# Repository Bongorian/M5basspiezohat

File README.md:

# M5basspiezohat

M5StickS3のHat2に接続する、ベース用の5チャンネル・ピエゾ入力基板。弦ごとの独立したピエゾ信号を高入力抵抗のバッファと音声ADCで処理し、TDMで本体へ送る。

本体で音程検出とUSB MIDI出力を行うESP-IDFファームウェアを含む。基板とファームウェアは実機未検証のR1試作版。

```text
独立ピエゾ ×4〜5 → 保護・バッファ・LPF → ES7210 ×2
                                      → TDM → M5StickS3
                                               → 音程検出・USB MIDI
```

## 仕様

| 項目 | R1 |
| --- | --- |
| 接続先 | M5StickS3 Hat2 |
| 入力 | 独立ピエゾ最大5チャンネル、内部SIG/GNDはんだパッド |
| ADC | ES7210×2、TDMカスケード接続 |
| 電源 | Hat2 EXT_5V、基板内でアナログ／デジタル3.3Vを生成 |
| 基板 | 21×38×1.0mm、4層、四隅R1mm |
| 実装 | 表面PCBA 101点。裏面は裸銅箔テストパッド4点 |
| 手実装 | ヘッダJ6、ピエゾ配線 |
| 筐体の設計範囲 | Hat単体・コネクタ込み48×24×15mm以内 |

## 設計データの利用

1. [基板仕様・接続表](hardware/sticks3-piezo-hat/README.md)で電源、Hat2端子、ピエゾ入力を確認する。
2. KiCad 9で [プロジェクト](hardware/sticks3-piezo-hat/sticks3-piezo-hat.kicad_pro)を開く。[回路図](hardware/sticks3-piezo-hat/sticks3-piezo-hat.kicad_sch)と[配線済み基板](hardware/sticks3-piezo-hat/sticks3-piezo-hat.kicad_pcb)が編集元。
3. 製造には [JLCPCB用データ一式](hardware/sticks3-piezo-hat/release/PCBA_JLCPCB.zip)と[製造・組立手順](hardware/sticks3-piezo-hat/manufacturing.md)を使用する。BOM、CPL、手実装部品の一覧を含む。
4. 変更後は[再生成・検査手順](hardware/sticks3-piezo-hat/README.md#ソースと再生成)に従い、製造データを再出力する。
5. [ファームウェアの導入・操作手順](firmware/README.md)に従ってM5StickS3へ書き込み、入力スロットを確認する。標準は5弦・共通MIDIチャンネル1・起動時ミュート・高速開始設定。[標準設定の書き込み用ZIP](firmware/release/m5basspiezohat-sticks3-0.2.1.zip)も使用できる。

## 検証状況

KiCad 9.0.9で未接続0件、DRC違反0件、ERC違反0件。回路図・基板・設計マニフェストの318接続を照合済み。[検査記録](hardware/sticks3-piezo-hat/validation.md)を参照。

Hat2ヘッダの嵌合、TDM取得、Low Bまでの周波数応答、弦間の振動漏れ、音程検出の遅延は未検証。[ファームウェア設計・評価手順](docs/firmware-design.md)に取得条件と評価項目を記載している。標準のUSBデバイスモードはUSBホストへ接続する。ホストモードも実装しているが、StickS3はUSB-Cへ給電しないため、音源側への外部VBUS給電と適切な接続回路が必要。

ファームウェアはESP-IDF v5.4.2でESP32-S3向けビルドを確認。合成信号による音程・発音・MIDIルーティングのホストテストを通過している。[CI](https://github.com/Bongorian/M5basspiezohat/actions/workflows/firmware.yml)でもビルドとテストを実行する。

[クロストーク分離・校正学習の検討](docs/crosstalk-separation.md)には固定行列とFIR分離の導入条件を記載。同期CSVから固定混合行列を学習するオフライン評価ツールを含む。リアルタイム分離と実機学習は未実装。

[Grove接続の外付けUSB MIDIホスト案](docs/grove-usb-midi-host.md)に、別USB端子を追加して本体USB-Cを維持する構成、通信・給電条件、LCSC部品候補を記載している。外部基板は未製作。

[筐体モデル](mechanical/sticks3-hat-concept.md)は寸法・保持構造の検討用。蓋と下端受けの固定方法、ケーブル出口は未設計。

## ファイル構成

| ディレクトリ | 内容 |
| --- | --- |
| `hardware/sticks3-piezo-hat/` | KiCad編集元、プロジェクト内ライブラリ、BOM、生成・検査ツール |
| `hardware/sticks3-piezo-hat/release/` | Gerber、PCBA用BOM/CPL、組立位置図、製造用ZIP |
| `mechanical/` | Blender筐体検討モデル、寸法計算、生成スクリプト |
| `docs/` | ファームウェア設計と評価手順 |
| `firmware/` | ESP-IDFアプリ、音程検出、USB MIDI、診断ツール、ホストテスト、書き込み用ZIP |

## ライセンス

KiCad由来のライブラリ・モデルとファームウェア依存ライブラリの出典・ライセンスは [NOTICE.md](NOTICE.md) を参照。プロジェクト独自部分の利用ライセンスは未指定。

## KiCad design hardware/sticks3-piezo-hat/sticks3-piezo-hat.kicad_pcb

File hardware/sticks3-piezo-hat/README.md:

# M5basspiezohat R1 — 基板仕様

弦ごとに独立したピエゾを最大5入力受け、ES7210×2のTDM出力をM5StickS3へ渡す。[付属ファームウェア](../../firmware/README.md)が音程検出とUSB MIDI出力を行う。基板・ファームウェアとも実機未検証。

**筐体の設計範囲：Hat単体・コネクタ込み48×24×15mm以内。** 基板は21×38×1.0mm、四隅R1mm、4層。ケース本体41.1×23.8×14.8mm。候補ヘッダC53207371のメーカー図面に基づくコネクタ込み公称長47.3mm、公差予算込み47.9mm。実機嵌合・造形精度は未確認で、寸法保証ではない。基板に固定穴・切り欠きはなく、筐体の左右ガイド溝と上下の受けで支える機構案。受けと蓋の留め方は未設計。[機構案](../../mechanical/sticks3-hat-concept.md)を参照。

## 設計検査

KiCad 9.0.9で未接続0件、DRC違反0件、回路図ERC違反0件。配線済み基板は [sticks3-piezo-hat.kicad_pcb](sticks3-piezo-hat.kicad_pcb)。2410配線セグメント／161ビア、回路図／基板／設計マニフェストの318接続が一致。部品本体は表面のみ、裏面はTP1〜4の裸銅箔。内層GND面の信号線は0、SMDパッドとビア穴の重なりは0。

[JLCPCB用データ一式](release/README.md)：[Gerber ZIP](release/Gerber_JLCPCB.zip)、[PCBA BOM](release/BOM_JLCPCB.csv)、[CPL](release/CPL_JLCPCB.csv)、[組立位置図](release/assembly-front.png)。BOMとCPLは101個の部品名が完全一致し、全点Top。CPLは品番別の回転補正を適用済み。D1〜D5もPCBA対象。J6とピエゾ線は手実装。U4の割り込み出力（13番ピン）はNC。ADC初期設定では割り込みを無効にする。

最小配線幅／間隔0.10／0.10mm、貫通ビア外径0.40mm・穴0.20mm、表裏テント、マスク開口1:1。[JLCPCBの能力表](https://jlcpcb.com/capabilities/pcb-capabilities)に対応するが、外径0.45mm未満・穴0.20mmのビアは追加料金対象なので、注文時に小径ビアの条件を指定する。製造条件と手実装の手順は [manufacturing.md](manufacturing.md)、検査記録は [validation.md](validation.md) を参照。

## 回路

| 回路 | 仕様 |
| --- | --- |
| 入力 | SIG/GND ×5組、内部はんだパッド、穴0.8mm・径1.8mm |
| 保護 | 47kΩ直列＋低漏れBAV199Wの2ダイオードクランプ |
| 入力負荷 | 10MΩを2個直列にした20MΩでVMIDへバイアス |
| バッファ | TLV9064IRTER ×2、3×3mm WQFN、利得1 |
| 中点 | 47kΩ分圧＋1µF→U2Bバッファ、約1.65V |
| LPF | 各入力1kΩ／47nFを2段、受動回路 |
| ADC結合 | P側10µF直列、N側10µFでAC接地。ADCのDCバイアスを分離 |
| ADC | ES7210 ×2、入力8スロット、うち5スロットを音程解析 |
| 電源 | EXT_5V→AP2112K-3.3 ×2、3V3A／3V3D |
| クロック | MCLK/BCLK/WSに33Ω、データ／カスケードにも33Ω |

受動LPFは2段の間にバッファがないため、独立したRCを2個掛けた特性と異なる。ADC入力負荷を無視した等しいR/Cの伝達は `1/(1+3sRC+(sRC)^2)`、合成-3dB周波数は約1.27kHz。R=1kΩ、C=47nFによる計算値で、ADC入力インピーダンスを含む実際の応答は測定する。アタックと倍音を残せるか、ADC内PGA・HPFと合わせて確認する。

Low B・30.87Hzを保つため、ピエゾ容量、20MΩ負荷、AC結合容量、ADC内部HPFをまとめて評価する。低漏れ保護の代わりに汎用BAV99や漏れの大きいSchottkyへ無確認で置き換えない。高抵抗入力付近は組み立て後にフラックスを清掃する。無給電時のピエゾ電圧による電源への回り込みも試験する。

## LCSC部品と実装分担

| 部品 | LCSC | 個数 | 分担 |
| --- | --- | ---: | --- |
| ES7210・4入力ADC | [C365743](https://www.lcsc.com/product-detail/C365743.html) | 2 | PCBA |
| TLV9064IRTER・3×3mm WQFN | [C882406](https://www.lcsc.com/product-detail/C882406.html) | 2 | PCBA |
| AP2112K-3.3TRG1 | [C51118](https://www.lcsc.com/product-detail/C51118.html) | 2 | PCBA |
| BAV199W・CBI・SOT-323 | [C51315120](https://www.lcsc.com/product-detail/C51315120.html) | 5 | PCBA |
| 10MΩ・SAE・0402 | [C54531017](https://www.lcsc.com/product-detail/C54531017.html) | 10 | PCBA |
| 1kΩ・0402 | [C11702](https://www.lcsc.com/product-detail/C11702.html) | 12 | PCBA |
| 33Ω・0402 | [C25105](https://www.lcsc.com/product-detail/C25105.html) | 5 | PCBA |
| 47kΩ・0603 | [C25819](https://www.lcsc.com/product-detail/C25819.html) | 8 | PCBA |
| 100nF・0402 | [C1525](https://www.lcsc.com/product-detail/C1525.html) | 6 | PCBA |
| 47nF・0402 | [C82219](https://www.lcsc.com/product-detail/C82219.html) | 10 | PCBA |
| 1µF・0402 | [C52923](https://www.lcsc.com/product-detail/C52923.html) | 25 | PCBA |
| 10µF・0603 | [C19702](https://www.lcsc.com/product-detail/C19702.html) | 14 | PCBA |
| 2×8・2.54mm L型ヘッダ・BXCONN | [C53207371](https://www.lcsc.com/product-detail/C53207371.html)・候補、実機嵌合未確認 | 1 | 手はんだ |
| ピエゾ線 | 基板内パッドへ接続 | 5組 | 手はんだ |

部品番号・数量・実装分担は [BOM_full.csv](BOM_full.csv) を基準とする。PCBAには [BOM_JLCPCB.csv](BOM_JLCPCB.csv)、手実装には [HAND_ASSEMBLY.csv](HAND_ASSEMBLY.csv) を使用する。LCSCの販売在庫とJLCPCBの実装用在庫・部品区分・調達価格は個別に確認する。

## Hat2接続

J6番号は **M5の外部Hat2端子表の番号**。M5内部回路図のCN2番号とは異なる。

| J6 | M5信号 | 本基板 |
| ---: | --- | --- |
| 1 | GND | GND |
| 2 | G5 | SCL |
| 3 | EXT_5V | 5V_HAT |
| 4 | G4 | SDA |
| 6 | G6 | WS |
| 7 | G1 | MCLK |
| 8 | G7 | BCLK |
| 9 | G8 | TDM DATA |
| その他 | BOOT/BAT/3V3/5VIN等 | 未接続 |

この番号とGPIOは [M5公式端子表](https://docs.m5stack.com/en/core/StickS3) に基づく。標準ヘッダのピン1マークと本体のGND位置は、選定した部品の視方向と実物で照合する。嵌合と挿入長は実機で確認する。

`M5.begin()`後、`M5.Power.setExtOutput(true)`でEXT_5Vを出力にする。本体GPIOは3.3V。EXT_5Vを出力にした状態で、その端子へ別電源を接続しない。

ADCの7bit I²CアドレスはU3＝0x40、U4＝0x41を想定したAD0/AD1接続。アドレスは実機で確認する。U3 TDMOUT→33Ω→U4 TDMIN、U4 TDMOUT→33Ω→J6 DATA。共通MCLK/BCLK/WSを使う。レジスタ設定は実機試験で確定する。

## 取得・MIDIの初期条件

16kS/s、8スロット×16bit、MCLK4.096MHz、BCLK2.048MHzを評価開始点とする。DMAは32フレーム×8本、合計4096B／16ms容量。2msごとに取得し、解析側へ渡す。詳細は [ファームウェア設計](../../docs/firmware-design.md) を参照。

Low Bの周期は約32.4ms。DMA待ちを短くしても、音程確定に必要な観測時間は残る。音声取得、音程解析、USB送信、音源発音の遅延を分けて測定する。USB MIDIは本体USB-Cを使い、音源のUSBホスト機能またはPC／USB MIDIホストを経由する。DIN出力回路はこのHatには載せていない。

## ソースと再生成

- `sticks3-piezo-hat.kicad_sch`：全ピンを明示した回路図
- `sticks3-piezo-hat.kicad_pcb`：配線済み最終基板
- `sticks3-piezo-hat-placement.kicad_pcb`：再生成用の配置版
- `PiezoHat.pretty/`、`PiezoHat.kicad_sym`：プロジェクト内ライブラリ
- `design.json`：ピン、型番、部品座標
- `BOM_JLCPCB.csv`：PCBA部品のみ、標準4列
- `jlc-rotation-corrections.json`：品番別のCPL回転補正。新しい品番へ変更したらプレビューを再確認
- `BOM_full.csv`、`HAND_ASSEMBLY.csv`：全調達／手実装
- `verify.py`、`verification.json`：接続と実装面の確認
- `preview/routed-front.png`、`preview/routed-board.glb`：最終基板の配線図・3D
- `release/`：Gerber、BOM、CPL、組立位置図、検査記録
- [ケースモデル](../../mechanical/sticks3-hat-concept.md)

KiCad 9.0.9の`kicad-cli`と`pcbnew`を読み込めるPythonが必要。Ubuntuでは`/usr/bin/python3`を使う。生成にはNumPy、図の出力にはPillow、補助ルータにはSciPyとC++17コンパイラを用意する。自動配線には別途`freerouting-cli`が必要。

```sh
cd hardware/sticks3-piezo-hat
/usr/bin/python3 generate.py
kicad-cli sch export netlist --format kicadxml -o schematic.xml sticks3-piezo-hat.kicad_sch
/usr/bin/python3 verify.py sticks3-piezo-hat-placement.kicad_pcb
/usr/bin/python3 route_compact.py sticks3-piezo-hat-placement.kicad_pcb NEW-routed.kicad_pcb
```

再生成は配置・回路図・BOMを上書きし、配線済み基板は別ファイルに保存する。KiCadのDSN出力へは0.127mm標準配線／0.10mm間隔、ビア径0.40mm・穴0.20mmを明示的に反映する。内層1はGND面、内層2は信号。QFN露出パッドの未充填ビアを禁止する。

## 組立・評価

[製造・組立手順](manufacturing.md)に従い、手実装部品とヘッダ方向を確認する。評価では電源・中点電圧、I²Cアドレス、ADC1個のTDM取得、2個のカスケード取得の順に確認する。ピエゾ接続後、Low Bの周波数応答、強いアタックでのクリップ、弦間漏れを測定する。

## 参照資料

メーカー資料：[ES7210レジスタ資料](https://files.waveshare.com/wiki/common/ES7210_DS.pdf)、[TLV9064](https://www.ti.com/lit/ds/symlink/tlv9064.pdf)、[CBI BAV199W](https://datasheet.lcsc.com/datasheet/pdf/08d81ae9ee2012e6b42c6110d851602f.pdf?productCode=C51315120)、[Espressif I²S/TDM/DMA](https://docs.espressif.com/projects/esp-idf/en/stable/esp32s3/api-reference/peripherals/i2s.html)。

## 製造データの再出力

リポジトリルートから実行する。配線済み基板を入力に、DRC／ERC・接続照合後、Gerber・BOM・CPL・ZIP・チェックサムを再出力する：

```sh
cd hardware/sticks3-piezo-hat
/usr/bin/python3 release.py
```

## 補助ルータ

`finish_route.py`用の補助ルータは `hardware/sticks3-piezo-hat/` で次のように構築する。生成・配線ツールは検討用で、毎回DRC／ERCと接続照合を行う。

```sh
mkdir -p .build
g++ -O3 -std=c++17 finish_astar.cpp -o .build/piezo-finish-astar
```

プロジェクト内のKiCad由来ライブラリについては [ライセンス文書](KICAD_LIBRARIES_LICENSE.md) と [出典](../../NOTICE.md) を参照。

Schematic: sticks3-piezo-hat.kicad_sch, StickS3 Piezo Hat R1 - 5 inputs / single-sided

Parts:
C1, C2, C32, C33, C43, C44: 100n; C_0402_1005Metric_AssemblyFront; LCSC C1525
C3, C4, C7, C8, C11, C12, C15, C16, C19, C20: 47n; C_0402_1005Metric_AssemblyFront; LCSC C82219
C5, C6, C9, C10, C13, C14, C17, C18, C21, C22, C51, C52, C53, C54: 10u; C_0603_1608Metric_AssemblyFront; LCSC C19702
C23, C24, C25, C26, C27, C28, C29, C30, C31, C34, C35, C36, C37, C38, C39, C40, C41, C42, C45, C46, C47, C48, C49, C50, C55: 1u; C_0402_1005Metric_AssemblyFront; LCSC C52923
D1, D2, D3, D4, D5: BAV199W; SOT-323_SC-70_AssemblyFront; LCSC C51315120
J1: PIEZO1; PiezoPair_P3.8
J2: PIEZO2; PiezoPair_P3.8
J3: PIEZO3; PiezoPair_P3.8
J4: PIEZO4; PiezoPair_P3.8
J5: PIEZO5; PiezoPair_P3.8
J6: HAT2_MANUAL; PinHeader_2x08_P2.54mm_Horizontal_AssemblyFront; LCSC C53207371
R1, R4, R7, R10, R13, R26, R28, R29: 47k; R_0603_1608Metric_AssemblyFront; LCSC C25819
R2, R3, R5, R6, R8, R9, R11, R12, R14, R15: 10M; R_0402_1005Metric_AssemblyFront; LCSC C54531017
R16, R17, R18, R19, R20, R21, R22, R23, R24, R25, R30, R31: 1k; R_0402_1005Metric_AssemblyFront; LCSC C11702
R32, R33, R34, R35, R36: 33R; R_0402_1005Metric_AssemblyFront; LCSC C25105
TP1: GND; TestPoint_Pad_D1.0mm_AssemblyFront
TP2: 3V3A; TestPoint_Pad_D1.0mm_AssemblyFront
TP3: 3V3D; TestPoint_Pad_D1.0mm_AssemblyFront
TP4: VMID; TestPoint_Pad_D1.0mm_AssemblyFront
U1, U2: TLV9064IRTER; QFN-16-1EP_3x3mm_P0.5mm_EP1.675x1.675mm_AssemblyFront; LCSC C882406
U3, U4: ES7210; ES7210_QFN32_4x4_P0.4_EP2.7; LCSC C365743
U5, U6: AP2112K-3.3TRG1; SOT-23-5_AssemblyFront; LCSC C51118

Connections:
3V3A: C1.1, C2.1, C30.1, C31.1, C41.1, C42.1, C52.1, D1.2 (K2/V+), D2.2 (K2/V+), D3.2 (K2/V+), D4.2 (K2/V+), D5.2 (K2/V+), R28.1, TP2.1, U1.2 (V+), U2.2 (V+), U3.22 (VDDA), U3.23 (VDDM), U4.22 (VDDA), U4.23 (VDDM), U5.5 (VOUT)
3V3D: C32.1, C33.1, C43.1, C44.1, C54.1, R26.2, R30.2, R31.2, TP3.1, U3.6 (VDDP), U3.7 (VDDD), U4.1 (AD0), U4.6 (VDDP), U4.7 (VDDD), U6.5 (VOUT)
5V_HAT: C51.1, C53.1, J6.3 (EXT_5V), U5.1 (VIN), U5.3 (EN), U6.1 (VIN), U6.3 (EN)
AIN1N: C6.1, U3.15 (MIC1N)
AIN1P: C5.2, U3.16 (MIC1P)
AIN2N: C10.1, U3.20 (MIC2N)
AIN2P: C9.2, U3.19 (MIC2P)
AIN3N: C14.1, U3.32 (MIC3N)
AIN3P: C13.2, U3.31 (MIC3P)
AIN4N: C18.1, U3.27 (MIC4N)
AIN4P: C17.2, U3.28 (MIC4P)
AIN5N: C22.1, U4.15 (MIC1N)
AIN5P: C21.2, U4.16 (MIC1P)
AIN6N: C46.1, U4.20 (MIC2N)
AIN6P: C45.1, U4.19 (MIC2P)
AIN7N: C48.1, U4.32 (MIC3N)
AIN7P: C47.1, U4.31 (MIC3P)
AIN8N: C50.1, U4.27 (MIC4N)
AIN8P: C49.1, U4.28 (MIC4P)
BCLK: R33.2, U3.9 (SCLK), U4.9 (SCLK)
BCLK_HAT: J6.8 (G7/BCLK), R33.1
BIAS1: R2.2, R3.1
BIAS2: R5.2, R6.1
BIAS3: R8.2, R9.1
BIAS4: R11.2, R12.1
BIAS5: R14.2, R15.1
BUF1: R16.1, U1.15 (OUTA), U1.16 (INA-)
BUF2: R18.1, U1.4 (INB-), U1.5 (OUTB)
BUF3: R20.1, U1.8 (OUTC), U1.9 (INC-)
BUF4: R22.1, U1.13 (IND-), U1.14 (OUTD)
BUF5: R24.1, U2.15 (OUTA), U2.16 (INA-)
CASCADE: R36.1, U3.11 (TDMOUT)
CASCADE_IN: R36.2, U4.12 (TDMIN)
GND: C1.2, C2.2, C3.2, C4.2, C6.2, C7.2, C8.2, C10.2, C11.2, C12.2, C14.2, C15.2, C16.2, C18.2, C19.2, C20.2, C22.2, C23.2, C24.2, C25.2, C26.2, C27.2, C28.2, C29.2, C30.2, C31.2, C32.2, C33.2, C34.2, C35.2, C36.2, C37.2, C38.2, C39.2, C40.2, C41.2, C42.2, C43.2, C44.2, C45.2, C46.2, C47.2, C48.2, C49.2, C50.2, C51.2, C52.2, C53.2, C54.2, C55.2, D1.1 (A1/GND), D2.1 (A1/GND), D3.1 (A1/GND), D4.1 (A1/GND), D5.1 (A1/GND), J1.2 (GND), J2.2 (GND), J3.2 (GND), J4.2 (GND), J5.2 (GND), J6.1 (GND), R29.2, TP1.1, U1.11 (V-), U1.17 (EP/V-), U2.11 (V-), U2.17 (EP/V-), U3.1 (AD0), U3.2 (AD1), U3.8 (GNDD), U3.12 (TDMIN), U3.21 (GNDA), U3.33 (EP), U4.2 (AD1), U4.8 (GNDD), U4.21 (GNDA), U4.33 (EP), U5.2 (GND), U6.2 (GND)
HI1: D1.3 (K1/A2/IN), R1.2, R2.1, U1.1 (INA+)
HI2: D2.3 (K1/A2/IN), R4.2, R5.1, U1.3 (INB+)
HI3: D3.3 (K1/A2/IN), R7.2, R8.1, U1.10 (INC+)
HI4: D4.3 (K1/A2/IN), R10.2, R11.1, U1.12 (IND+)
HI5: D5.3 (K1/A2/IN), R13.2, R14.1, U2.1 (INA+)
INT3: R26.1, U3.13 (INT)
LP1A: C3.1, R16.2, R17.1
LP1B: C4.1, C5.1, R17.2
LP2A: C7.1, R18.2, R19.1
LP2B: C8.1, C9.1, R19.2
LP3A: C11.1, R20.2, R21.1
LP3B: C12.1, C13.1, R21.2
LP4A: C15.1, R22.2, R23.1
LP4B: C16.1, C17.1, R23.2
LP5A: C19.1, R24.2, R25.1
LP5B: C20.1, C21.1, R25.2
MCLK: R32.2, U3.5 (MCLK), U4.5 (MCLK)
MCLK_HAT: J6.7 (G1/MCLK), R32.1
PZ1: J1.1 (SIG), R1.1
PZ2: J2.1 (SIG), R4.1
PZ3: J3.1 (SIG), R7.1
PZ4: J4.1 (SIG), R10.1
PZ5: J5.1 (SIG), R13.1
SCL: J6.2 (G5/SCL), R31.1, U3.4 (CCLK), U4.4 (CCLK)
SDA: J6.4 (G4/SDA), R30.1, U3.3 (CDATA), U4.3 (CDATA)
SPARE_C: U2.8 (OUTC), U2.9 (INC-)
SPARE_D: U2.13 (IND-), U2.14 (OUTD)
TDM_HAT: J6.9 (G8/DATA), R35.2
TDM_OUT: R35.1, U4.11 (TDMOUT)
U3_MICBIAS12: C25.1, U3.24 (MICBIAS12)
U3_MICBIAS34: C27.1, U3.26 (MICBIAS34)
U3_REFP12: C23.1, U3.17 (REFP12)
U3_REFP34: C28.1, U3.29 (REFP34)
U3_REFQ12: C24.1, U3.18 (REFQ12)
U3_REFQ34: C29.1, U3.30 (REFQ34)
U3_REFQM: C26.1, U3.25 (REFQM)
U4_MICBIAS12: C36.1, U4.24 (MICBIAS12)
U4_MICBIAS34: C38.1, U4.26 (MICBIAS34)
U4_REFP12: C34.1, U4.17 (REFP12)
U4_REFP34: C39.1, U4.29 (REFP34)
U4_REFQ12: C35.1, U4.18 (REFQ12)
U4_REFQ34: C40.1, U4.30 (REFQ34)
U4_REFQM: C37.1, U4.25 (REFQM)
VDIV: C55.1, R28.2, R29.1, U2.3 (INB+), U2.10 (INC+), U2.12 (IND+)
VMID: R3.2, R6.2, R9.2, R12.2, R15.2, TP4.1, U2.4 (INB-), U2.5 (OUTB)
WS: R34.2, U3.10 (LRCK), U4.10 (LRCK)
WS_HAT: J6.6 (G6/WS), R34.1

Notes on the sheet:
STRING 1: 20M load / unity buffer / passive two-pole LPF / AC isolated ADC
STRING 2: 20M load / unity buffer / passive two-pole LPF / AC isolated ADC
STRING 3: 20M load / unity buffer / passive two-pole LPF / AC isolated ADC
STRING 4: 20M load / unity buffer / passive two-pole LPF / AC isolated ADC
STRING 5: 20M load / unity buffer / passive two-pole LPF / AC isolated ADC
BUFFERS: U1 A-D = strings 1-4; U2 A = string 5; U2 B = VMID; C/D terminated
DECOUPLING / BIAS / CLOCK TERMINATION / TEST: all pins and nets explicit
ADC3 = address 0x40 / inputs 1-4; ADC4 = 0x41 / input 5 plus unused inputs 6-8

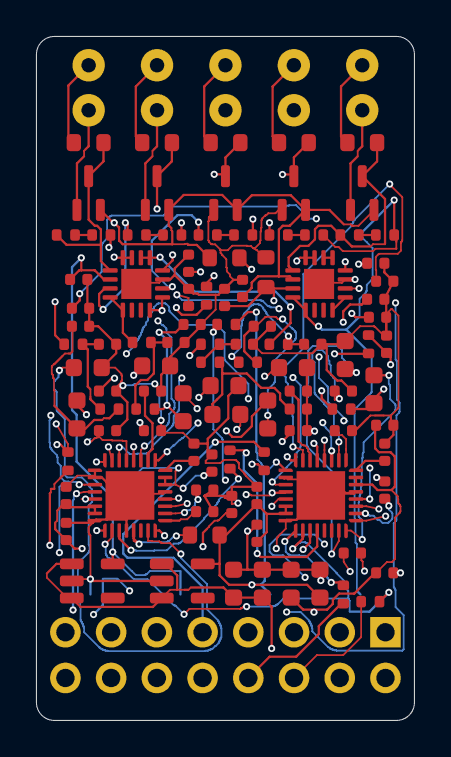
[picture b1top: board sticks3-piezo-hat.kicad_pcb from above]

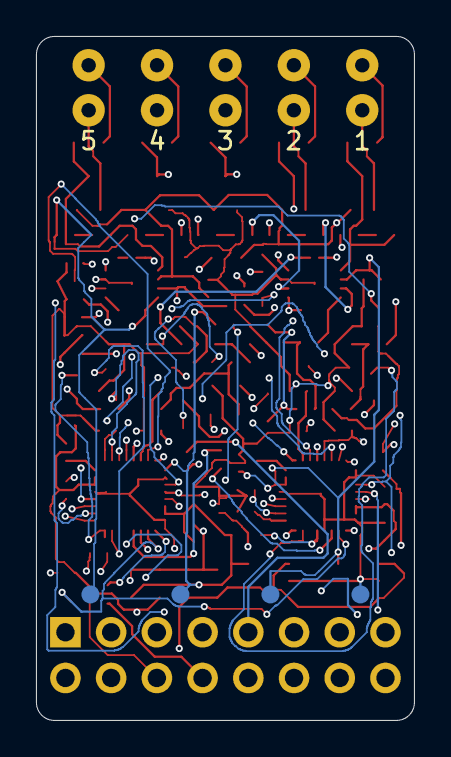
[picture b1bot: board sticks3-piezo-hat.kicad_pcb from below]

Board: 4 copper layers, 21.0 x 38.0 mm, 111 parts (4 on the bottom side), 81 nets.

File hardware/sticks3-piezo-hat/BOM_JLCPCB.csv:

Comment,Designator,Footprint,LCSC Part #
47k,"R1,R4,R7,R10,R13,R26,R28,R29",PiezoHat:R_0603_1608Metric_AssemblyFront,C25819
10M,"R2,R3,R5,R6,R8,R9,R11,R12,R14,R15",PiezoHat:R_0402_1005Metric_AssemblyFront,C54531017
BAV199W,"D1,D2,D3,D4,D5",PiezoHat:SOT-323_SC-70_AssemblyFront,C51315120
TLV9064IRTER,"U1,U2",PiezoHat:QFN-16-1EP_3x3mm_P0.5mm_EP1.675x1.675mm_AssemblyFront,C882406
100n,"C1,C2,C32,C33,C43,C44",PiezoHat:C_0402_1005Metric_AssemblyFront,C1525
1k,"R16,R17,R18,R19,R20,R21,R22,R23,R24,R25,R30,R31",PiezoHat:R_0402_1005Metric_AssemblyFront,C11702
47n,"C3,C4,C7,C8,C11,C12,C15,C16,C19,C20",PiezoHat:C_0402_1005Metric_AssemblyFront,C82219
10u,"C5,C6,C9,C10,C13,C14,C17,C18,C21,C22,C51,C52,C53,C54",PiezoHat:C_0603_1608Metric_AssemblyFront,C19702
ES7210,"U3,U4",PiezoHat:ES7210_QFN32_4x4_P0.4_EP2.7,C365743
1u,"C23,C24,C25,C26,C27,C28,C29,C30,C31,C34,C35,C36,C37,C38,C39,C40,C41,C42,C45,C46,C47,C48,C49,C50,C55",PiezoHat:C_0402_1005Metric_AssemblyFront,C52923
AP2112K-3.3TRG1,"U5,U6",PiezoHat:SOT-23-5_AssemblyFront,C51118
33R,"R32,R33,R34,R35,R36",PiezoHat:R_0402_1005Metric_AssemblyFront,C25105

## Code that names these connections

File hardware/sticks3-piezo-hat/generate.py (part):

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for i,(o,m,p) in enumerate([(15,16,1),(5,4,3),(8,9,10),(14,13,12)],1):
 oppins[o]=oppins[m]=f'BUF{i}';oppins[p]=f'HI{i}'
add('U1','OP','TLV9064IRTER',{str(n):v for n,v in oppins.items()},5.55,16.7,0,'buffers')
oppins={15:'BUF5',16:'BUF5',1:'HI5',2:'3V3A',3:'VDIV',4:'VMID',5:'VMID',8:'SPARE_C',9:'SPARE_C',10:'VDIV',11:'GND',12:'VDIV',13:'SPARE_D',14:'SPARE_D',17:'GND'}
add('U2','OP','TLV9064IRTER',{str(n):v for n,v in oppins.items()},15.7,16.7,0,'buffers')
cap('C100n','100n','3V3A',1.0,16.7,90,'buffers')
cap('C100n','100n','3V3A',10.7,16.7,90,'buffers')
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for index,x in [(3,5.2),(4,15.8)]:
 pins={1:'GND' if index==3 else '3V3D',2:'GND',3:'SDA',4:'SCL',5:'MCLK',6:'3V3D',7:'3V3D',8:'GND',9:'BCLK',10:'WS',11:'CASCADE' if index==3 else 'TDM_OUT',12:'GND' if index==3 else 'CASCADE_IN',13:f'INT{index}',14:None,21:'GND',22:'3V3A',23:'3V3A',33:'GND'}
 for p in [17,18,24,25,26,29,30]: pins[p]=f'U{index}_{adc_names[p]}'
 for ch,(p,n) in enumerate([(16,15),(19,20),(31,32),(28,27)],1):
  channel=ch if index==3 else ch+4
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for a,b,x,y in [('MCLK_HAT','MCLK',1.8,41.0),('BCLK_HAT','BCLK',4.1,41.0),('WS_HAT','WS',6.4,41.0),('TDM_OUT','TDM_HAT',18.5,35.0),('CASCADE','CASCADE_IN',10.5,31.5)]:
 passive('R','R33','33R',a,b,x,y,0,'digital')

hatpins={'1':'GND','2':'SCL','3':'5V_HAT','4':'SDA','5':None,'6':'WS_HAT','7':'MCLK_HAT','8':'BCLK_HAT','9':'TDM_HAT','10':None,'11':None,'12':None,'13':None,'14':None,'15':None,'16':None}
add('J6','HAT','HAT2_MANUAL',hatpins,19.39,41.0,270,'host')
for i,(value,x,y) in enumerate([('GND',10.5,35.0),('3V3A',10.5,37.0),('3V3D',10.5,39.0),('VMID',10.5,10.8)],1):
 add('TP'+str(i),'TP',value,{'1':value},x,y,0,'test')
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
